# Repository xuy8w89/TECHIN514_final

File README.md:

### On-table drinking reminder

##### Overview

This project aims to design a wireless smart water monitoring system that tracks the water volume in a cup placed on a table and reminds users to drink water in a timely manner. By combining capacitive sensing, wireless communication, and algorithmic processing, the system supports healthier daily hydration habits with minimal user intervention.

##### Idea

The core idea is to wirelessly monitor the water volume on a table (visualized by needle gauge) and provide intelligent drinking reminders based on real-time sensing and usage patterns. The system continuously estimates the remaining water volume and determines when a reminder (LED) should be triggered.

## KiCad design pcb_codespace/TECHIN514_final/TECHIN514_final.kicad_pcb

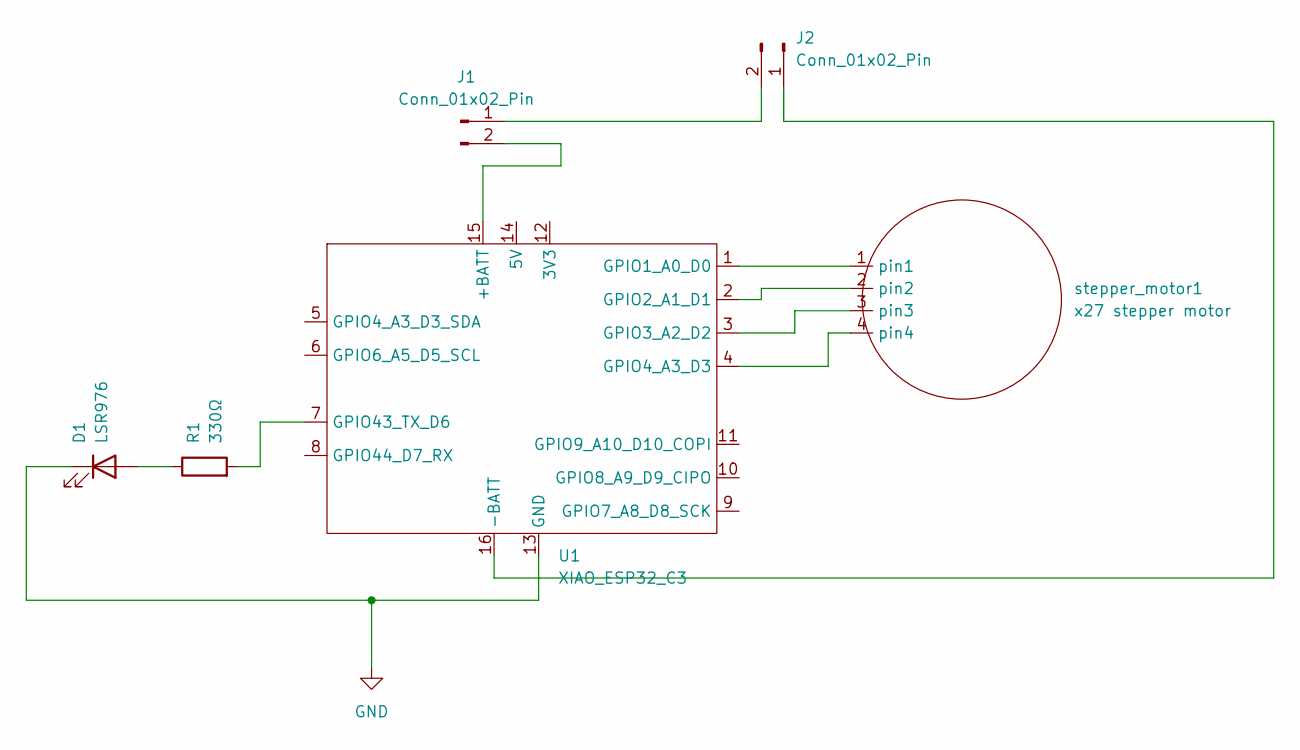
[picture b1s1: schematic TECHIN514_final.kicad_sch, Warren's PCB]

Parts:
D1: LSR976; LED_0805_2012Metric_Pad1.15x1.40mm_HandSolder
J1, J2: Conn_01x02_Pin; PinHeader_1x02_P1.00mm_Vertical
R1: 330Ω; R_0603_1608Metric_Pad0.98x0.95mm_HandSolder
U1: XIAO_ESP32_C3; XIAO_ESP32
stepper_motor1: x27 stepper motor; x27_stepper

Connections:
GND: D1.1 (K), U1.13 (GND)
unnamed: D1.2 (A), R1.1
unnamed: J1.1, J2.2
unnamed: J1.2, U1.15 (+BATT)
unnamed: J2.1, U1.16 (-BATT)
unnamed: U1.1 (GPIO1_A0_D0), stepper_motor1.1
unnamed: U1.2 (GPIO2_A1_D1), stepper_motor1.2
unnamed: U1.3 (GPIO3_A2_D2), stepper_motor1.3
unnamed: U1.4 (GPIO4_A3_D3), stepper_motor1.4
unnamed: R1.2, U1.7 (GPIO43_TX_D6)

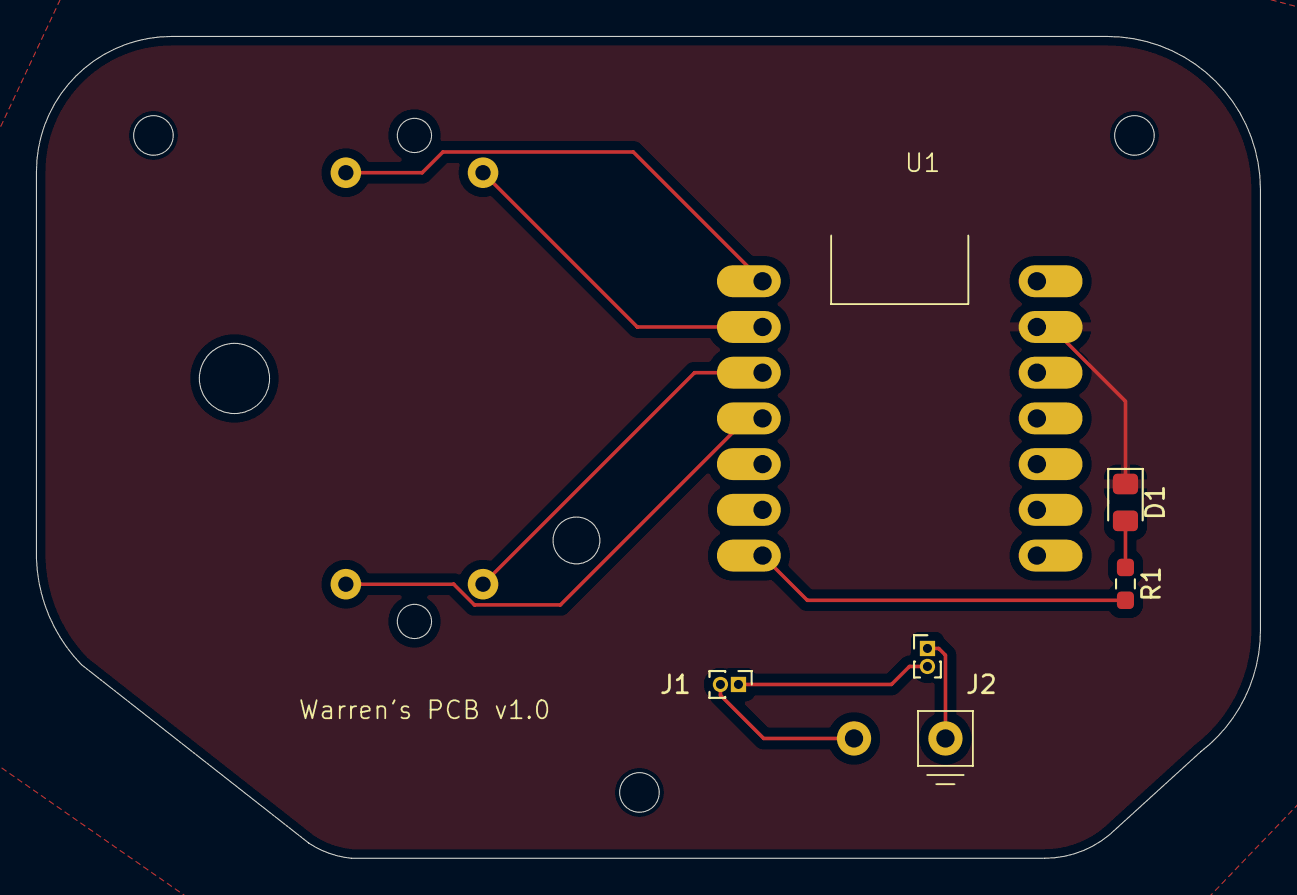
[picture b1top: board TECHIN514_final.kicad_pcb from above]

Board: 2 copper layers, 68.0 x 45.7 mm, 6 parts (0 on the bottom side), 10 nets.

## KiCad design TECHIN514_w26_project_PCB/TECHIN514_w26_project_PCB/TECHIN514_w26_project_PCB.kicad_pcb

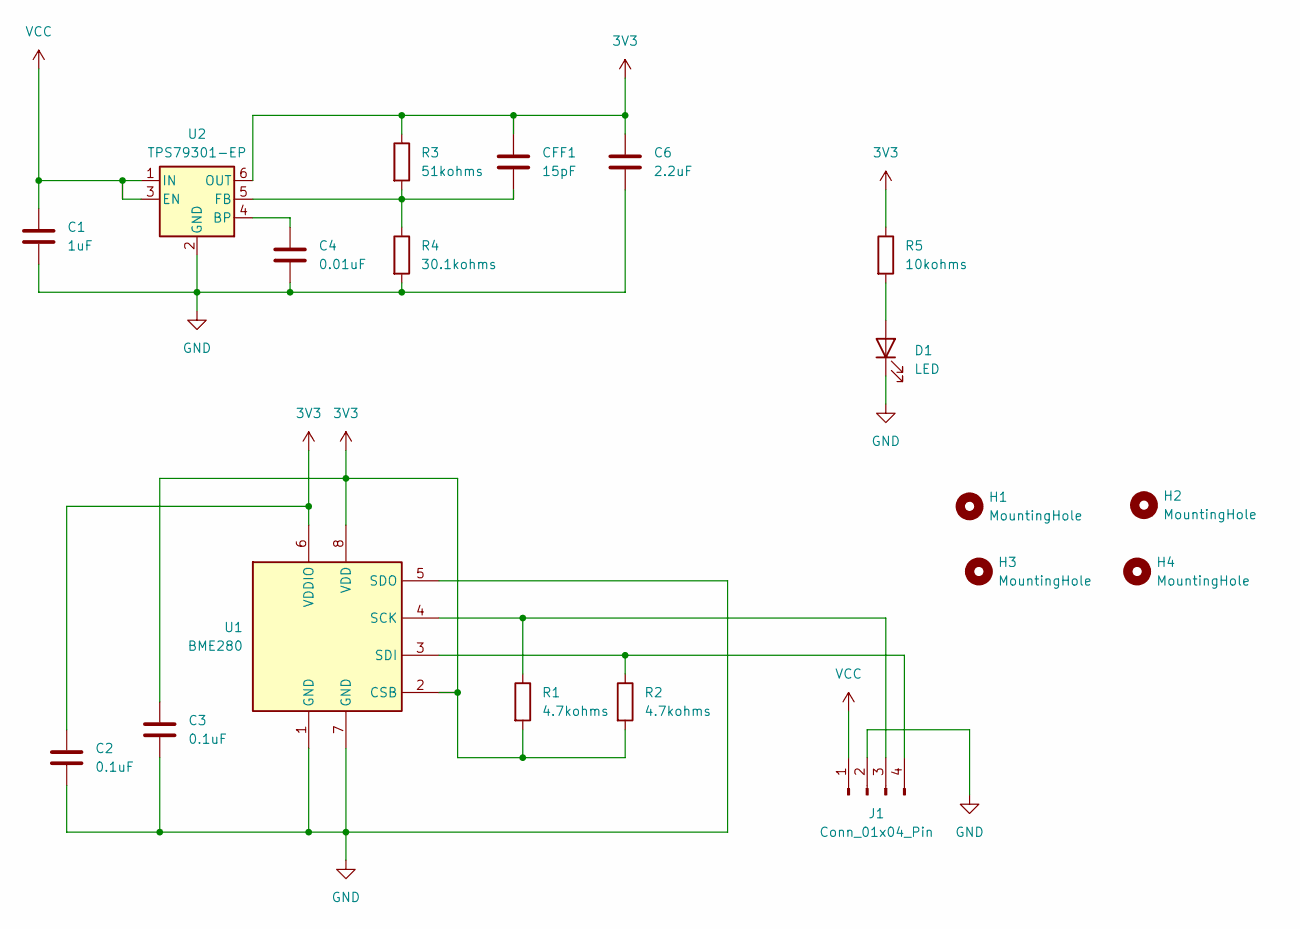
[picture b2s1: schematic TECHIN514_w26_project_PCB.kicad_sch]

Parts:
C1: 1uF; C_0402_1005Metric_Pad0.74x0.62mm_HandSolder
C2, C3: 0.1uF; C_0402_1005Metric_Pad0.74x0.62mm_HandSolder
C4: 0.01uF; C_0402_1005Metric_Pad0.74x0.62mm_HandSolder
C6: 2.2uF; C_0402_1005Metric_Pad0.74x0.62mm_HandSolder
CFF1: 15pF; C_0402_1005Metric_Pad0.74x0.62mm_HandSolder
D1: LED; LED_0402_1005Metric_Pad0.77x0.64mm_HandSolder
H1, H2, H3, H4: MountingHole; MountingHole_2.2mm_M2
J1: Conn_01x04_Pin; PinHeader_1x04_P1.00mm_Horizontal
R1, R2: 4.7kohms; R_0402_1005Metric_Pad0.72x0.64mm_HandSolder
R3: 51kohms; R_0402_1005Metric_Pad0.72x0.64mm_HandSolder
R4: 30.1kohms; R_0402_1005Metric_Pad0.72x0.64mm_HandSolder
R5: 10kohms; R_0402_1005Metric_Pad0.72x0.64mm_HandSolder
U1: BME280; Bosch_LGA-8_2.5x2.5mm_P0.65mm_ClockwisePinNumbering
U2: TPS79301-EP; SOT-23-6

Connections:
3V3: C2.1, C3.1, C6.1, CFF1.1, R1.2, R2.2, R3.1, R5.1, U1.2 (CSB), U1.6 (VDDIO), U1.8 (VDD), U2.6 (OUT)
GND: C1.2, C2.2, C3.2, C4.2, C6.2, D1.1 (K), J1.2, R4.2, U1.1 (GND), U1.5 (SDO), U1.7 (GND), U2.2 (GND)
unnamed: D1.2 (A), R5.2
unnamed: J1.3, R1.1, U1.4 (SCK)
unnamed: J1.4, R2.1, U1.3 (SDI)
unnamed: C4.1, U2.4 (BP)
unnamed: CFF1.2, R3.2, R4.1, U2.5 (FB)
VCC: C1.1, J1.1, U2.1 (IN), U2.3 (EN)

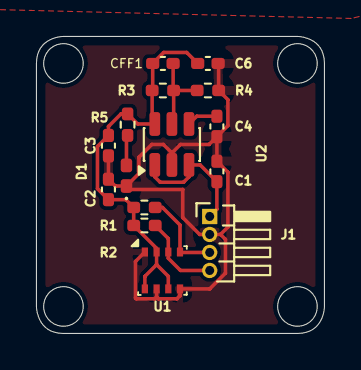
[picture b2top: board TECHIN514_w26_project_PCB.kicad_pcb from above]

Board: 2 copper layers, 16.0 x 16.5 mm, 19 parts (0 on the bottom side), 8 nets.

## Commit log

2026-01-15 initializing
2026-01-20 submission
2026-01-27 kicad
2026-02-04 lab 4
2026-02-10 pcb_upload
2026-03-16 test
